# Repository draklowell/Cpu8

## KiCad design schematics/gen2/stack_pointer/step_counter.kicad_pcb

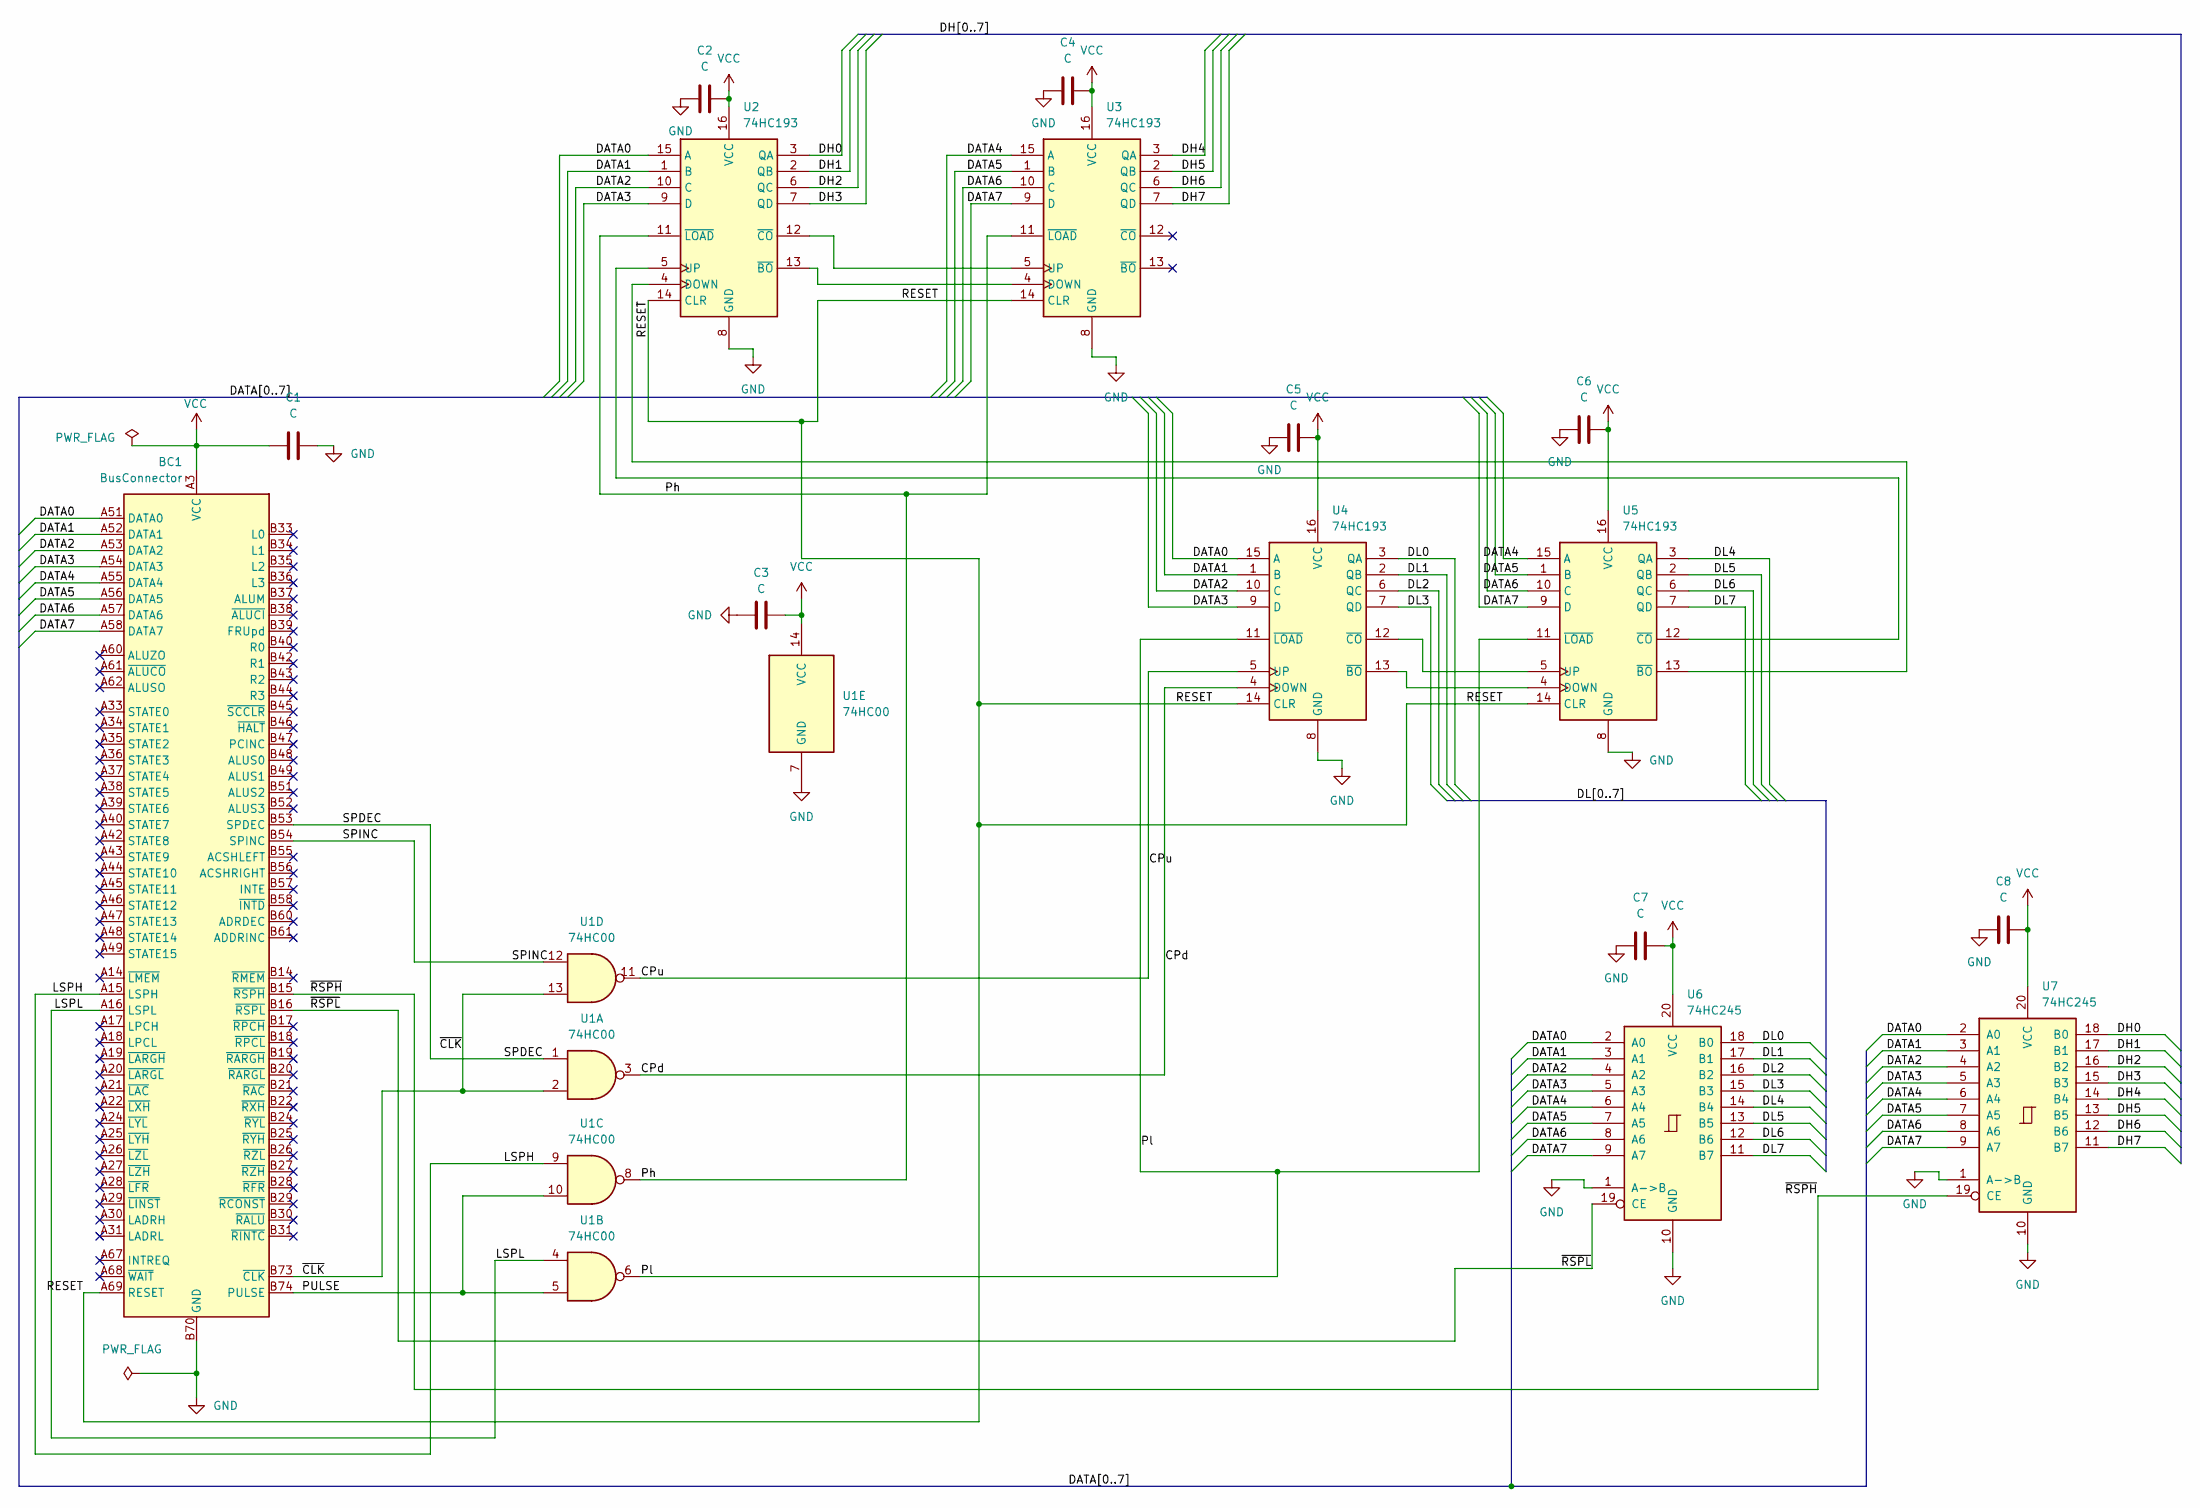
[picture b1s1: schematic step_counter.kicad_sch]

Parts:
BC1: BusConnector; BUS_PCIexpress_x16
C1: C; C_Radial_D6.3mm_H5.0mm_P2.50mm
C2, C3, C4, C5, C6, C7, C8: C; C_Disc_D3.0mm_W1.6mm_P2.50mm
U1: 74HC00; DIP-14_W7.62mm_Socket_LongPads
U2, U3, U4, U5: 74HC193; DIP-16_W7.62mm_Socket_LongPads
U6, U7: 74HC245; DIP-20_W7.62mm_Socket_LongPads

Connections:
/CPd: U1.3, U4.4 (DOWN)
/CPu: U1.11, U4.5 (UP)
/DATA0: BC1.A51 (DATA0), U2.15 (A), U4.15 (A), U6.2 (A0), U7.2 (A0)
/DATA1: BC1.A52 (DATA1), U2.1 (B), U4.1 (B), U6.3 (A1), U7.3 (A1)
/DATA2: BC1.A53 (DATA2), U2.10 (C), U4.10 (C), U6.4 (A2), U7.4 (A2)
/DATA3: BC1.A54 (DATA3), U2.9 (D), U4.9 (D), U6.5 (A3), U7.5 (A3)
/DATA4: BC1.A55 (DATA4), U3.15 (A), U5.15 (A), U6.6 (A4), U7.6 (A4)
/DATA5: BC1.A56 (DATA5), U3.1 (B), U5.1 (B), U6.7 (A5), U7.7 (A5)
/DATA6: BC1.A57 (DATA6), U3.10 (C), U5.10 (C), U6.8 (A6), U7.8 (A6)
/DATA7: BC1.A58 (DATA7), U3.9 (D), U5.9 (D), U6.9 (A7), U7.9 (A7)
/DH0: U2.3 (QA), U7.18 (B0)
/DH1: U2.2 (QB), U7.17 (B1)
/DH2: U2.6 (QC), U7.16 (B2)
/DH3: U2.7 (QD), U7.15 (B3)
/DH4: U3.3 (QA), U7.14 (B4)
/DH5: U3.2 (QB), U7.13 (B5)
/DH6: U3.6 (QC), U7.12 (B6)
/DH7: U3.7 (QD), U7.11 (B7)
/DL0: U4.3 (QA), U6.18 (B0)
/DL1: U4.2 (QB), U6.17 (B1)
/DL2: U4.6 (QC), U6.16 (B2)
/DL3: U4.7 (QD), U6.15 (B3)
/DL4: U5.3 (QA), U6.14 (B4)
/DL5: U5.2 (QB), U6.13 (B5)
/DL6: U5.6 (QC), U6.12 (B6)
/DL7: U5.7 (QD), U6.11 (B7)
/LSPH: BC1.A15 (LSPH), U1.9
/LSPL: BC1.A16 (LSPL), U1.4
/PULSE: BC1.B74 (PULSE), U1.5, U1.10
/Ph: U1.8, U2.11 (~LOAD), U3.11 (~LOAD)
/Pl: U1.6, U4.11 (~LOAD), U5.11 (~LOAD)
/RESET: BC1.A69 (RESET), U2.14 (CLR), U3.14 (CLR), U4.14 (CLR), U5.14 (CLR)
/SPDEC: BC1.B53 (SPDEC), U1.1
/SPINC: BC1.B54 (SPINC), U1.12
/~CLK: BC1.B73 (~CLK), U1.2, U1.13
/~RSPH: BC1.B15 (~RSPH), U7.19 (CE)
/~RSPL: BC1.B16 (~RSPL), U6.19 (CE)
GND: BC1.A12 (GND), BC1.A13 (GND), BC1.A23 (GND), BC1.A32 (GND), BC1.A41 (GND), BC1.A50 (GND), BC1.A59 (GND), BC1.A63 (GND), BC1.A64 (GND), BC1.A65 (GND), BC1.A66 (GND), BC1.A70 (GND), BC1.A71 (GND), BC1.A72 (GND), BC1.A73 (GND), BC1.A74 (GND), BC1.A75 (GND), BC1.A76 (GND), BC1.B12 (GND), BC1.B13 (GND), BC1.B23 (GND), BC1.B32 (GND), BC1.B41 (GND), BC1.B50 (GND), BC1.B59 (GND), BC1.B62 (GND), BC1.B63 (GND), BC1.B64 (GND), BC1.B65 (GND), BC1.B66 (GND), BC1.B67 (GND), BC1.B68 (GND), BC1.B69 (GND), BC1.B70 (GND), BC1.B71 (GND), BC1.B72 (GND), BC1.B75 (GND), BC1.B76 (GND), C1.2, C2.1, C3.1, C4.1, C5.1, C6.1, C7.2, C8.2, U1.7 (GND), U2.8 (GND), U3.8 (GND), U4.8 (GND), U5.8 (GND), U6.1 (A->B), U6.10 (GND), U7.1 (A->B), U7.10 (GND)
unnamed: U2.4 (DOWN), U5.13 (~BO)
unnamed: U2.5 (UP), U5.12 (~CO)
unnamed: U2.13 (~BO), U3.4 (DOWN)
unnamed: U2.12 (~CO), U3.5 (UP)
unnamed: U4.13 (~BO), U5.4 (DOWN)
unnamed: U4.12 (~CO), U5.5 (UP)
VCC: BC1.A1 (VCC), BC1.A2 (VCC), BC1.A3 (VCC), BC1.A4 (VCC), BC1.A5 (VCC), BC1.B1 (VCC), BC1.B2 (VCC), BC1.B3 (VCC), BC1.B4 (VCC), BC1.B5 (VCC), C1.1, C2.2, C3.2, C4.2, C5.2, C6.2, C7.1, C8.1, U1.14 (VCC), U2.16 (VCC), U3.16 (VCC), U4.16 (VCC), U5.16 (VCC), U6.20 (VCC), U7.20 (VCC)

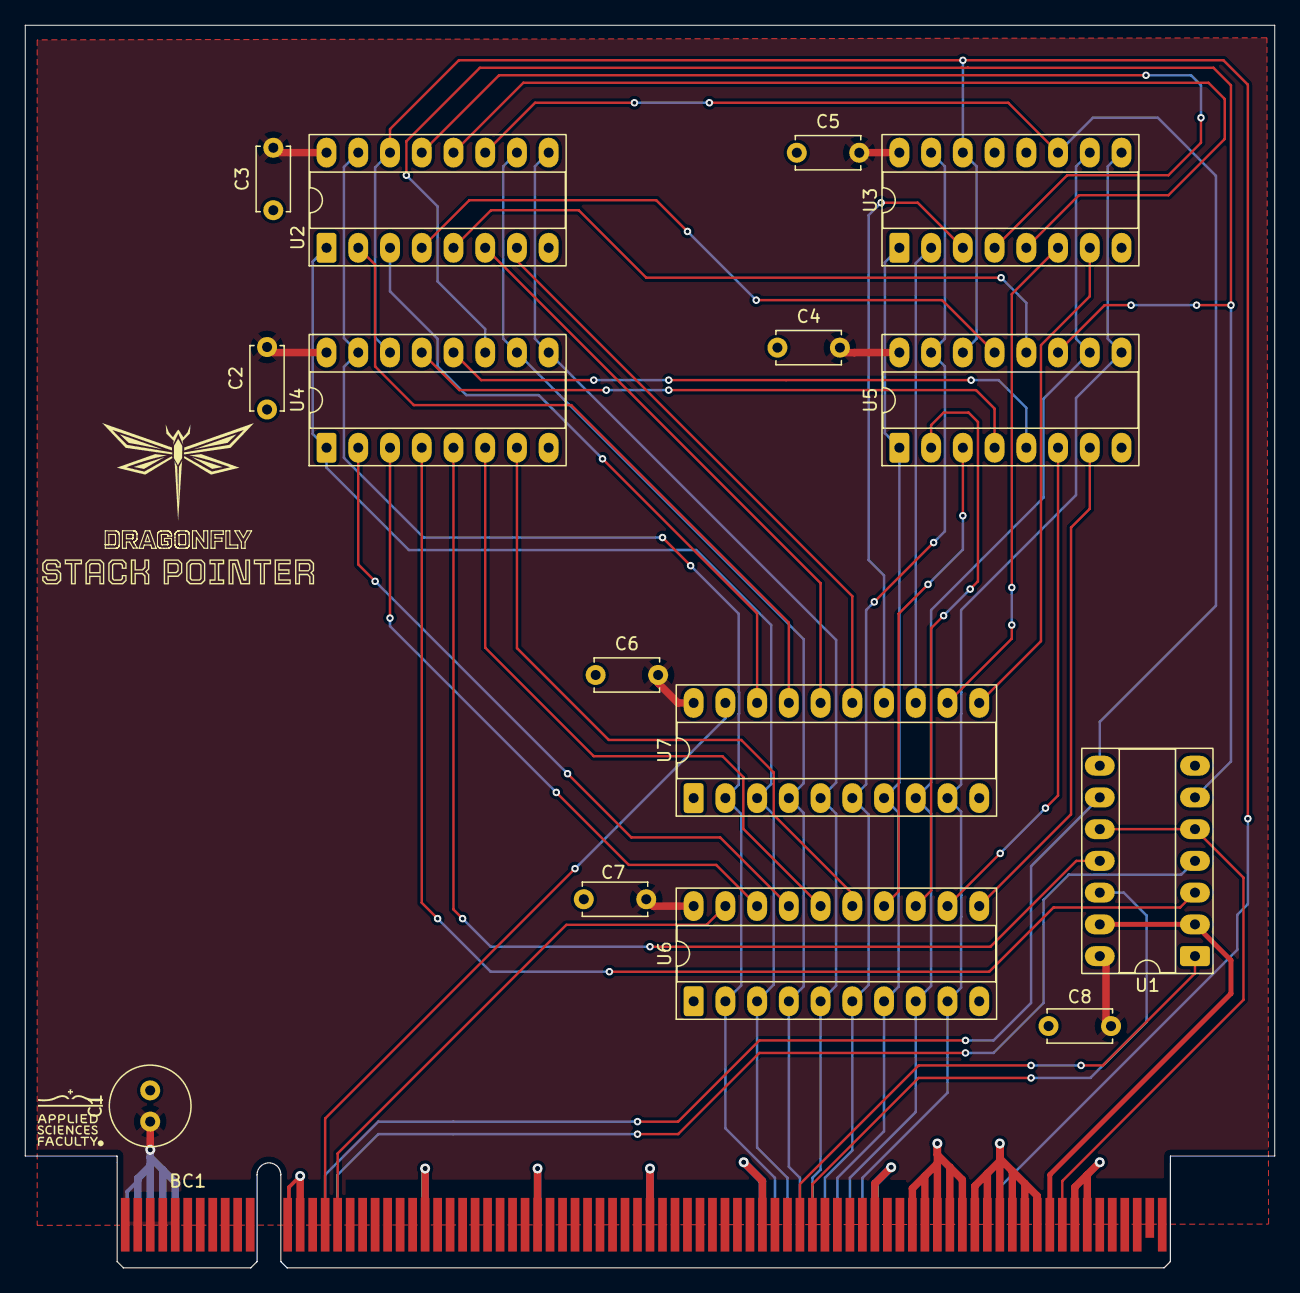
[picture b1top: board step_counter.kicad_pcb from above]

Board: 2 copper layers, 100.0 x 99.4 mm, 17 parts (0 on the bottom side), 45 nets.

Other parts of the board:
kibuzzard-6911C575: G***; kibuzzard-6911C575

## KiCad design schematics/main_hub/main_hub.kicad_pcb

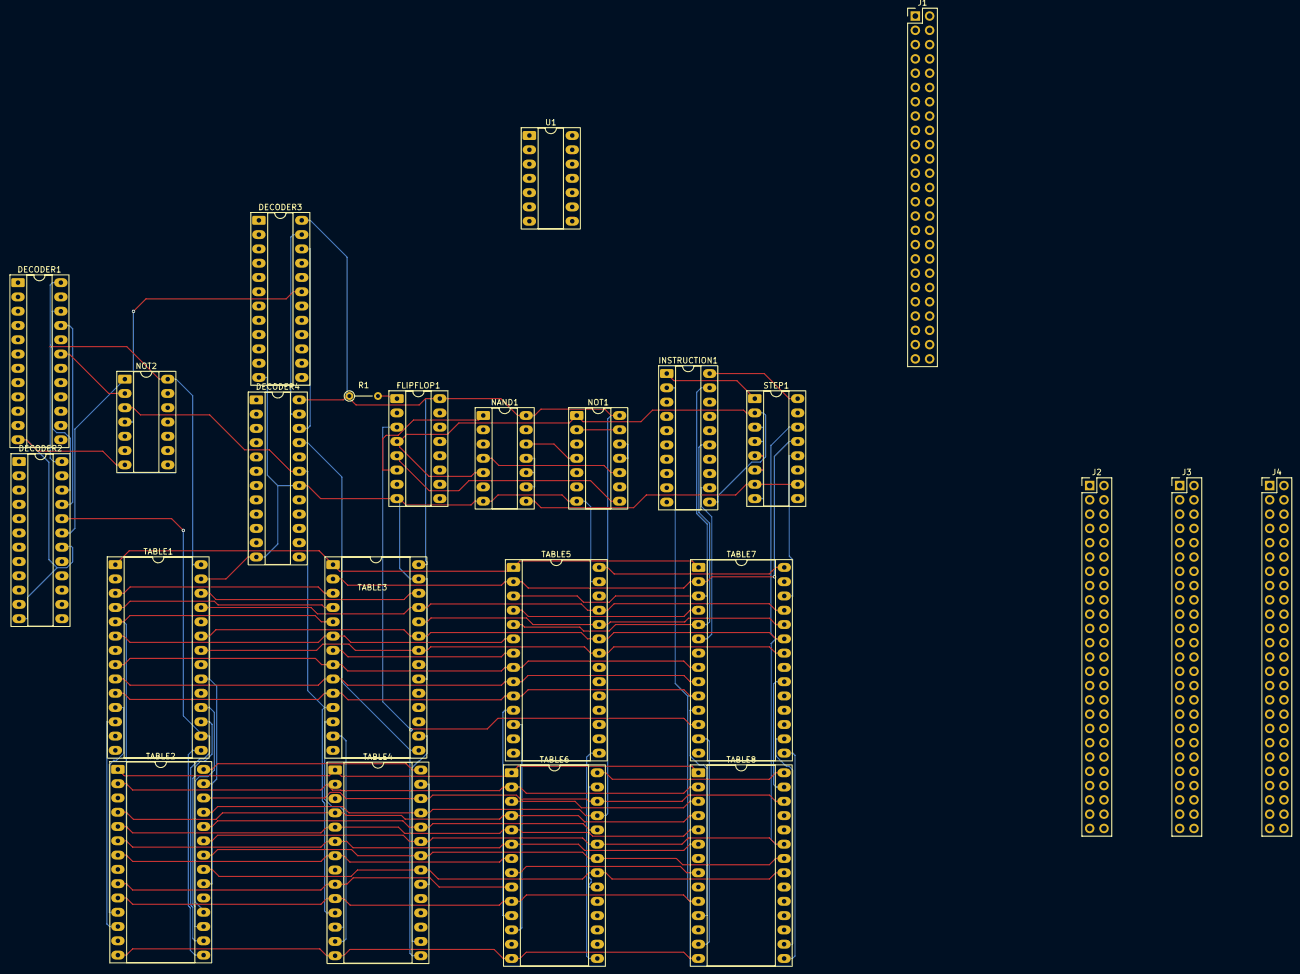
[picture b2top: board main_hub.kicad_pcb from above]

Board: 2 copper layers, 24 parts (0 on the bottom side), 90 nets.

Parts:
DECODER1, DECODER2, DECODER3, DECODER4: 74LS154; DIP-24_W7.62mm_Socket_LongPads
FLIPFLOP1: 74LS109; DIP-16_W7.62mm_Socket_LongPads
INSTRUCTION1: 74LS273; DIP-20_W7.62mm_Socket_LongPads
J1, J2, J3, J4: Conn_02x25_Counter_Clockwise; PinHeader_2x25_P2.54mm_Vertical
NAND1: 74LS00; DIP-14_W7.62mm_Socket_LongPads
NOT1, NOT2: 74LS04; DIP-14_W7.62mm_Socket_LongPads
R1: 5kOhm; R_Axial_DIN0204_L3.6mm_D1.6mm_P5.08mm_Vertical
STEP1: 74LS161; DIP-16_W7.62mm_Socket_LongPads
TABLE1, TABLE2, TABLE3, TABLE4, TABLE5, TABLE6, TABLE7, TABLE8: 28C256; DIP-28_W15.24mm_Socket_LongPads
U1: 74LS02; DIP-14_W7.62mm_Socket_LongPads

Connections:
/ALUM: J1.31, TABLE1.17 (D5), TABLE2.17 (D5)
/ALUS0: J1.35, TABLE5.11 (D0), TABLE6.11 (D0)
/ALUS1: J1.34, TABLE5.12 (D1), TABLE6.12 (D1)
/ALUS2: J1.33, TABLE5.13 (D2), TABLE6.13 (D2)
/ALUS3: J1.32, TABLE5.15 (D3), TABLE6.15 (D3)
/ALUSignOut: J1.38, J2.23
/ALUZeroOut: J1.36, J2.21
/AccumShiftLeft: J1.29, TABLE5.18 (D6), TABLE6.18 (D6)
/AccumShiftRight: J1.28, TABLE5.19 (D7), TABLE6.19 (D7)
/AddrDecrement: TABLE7.13 (D2), TABLE8.13 (D2)
/AddrIncrement: TABLE7.15 (D3), TABLE8.15 (D3)
/BUS0: INSTRUCTION1.3 (D0), J1.11, J2.11, J3.11, J4.11
/BUS1: INSTRUCTION1.4 (D1), J1.12, J2.12, J3.12, J4.12
/BUS2: INSTRUCTION1.7 (D2), J1.13, J2.13, J3.13, J4.13
/BUS3: INSTRUCTION1.8 (D3), J1.14, J2.14, J3.14, J4.14
/BUS4: INSTRUCTION1.13 (D4), J1.15, J2.15, J3.15, J4.15
/BUS5: INSTRUCTION1.14 (D5), J1.16, J2.16, J3.16, J4.16
/BUS6: INSTRUCTION1.17 (D6), J1.17, J2.17, J3.17, J4.17
/BUS7: INSTRUCTION1.18 (D7), J1.18, J2.18, J3.18, J4.18
/Clk: FLIPFLOP1.4 (C), J1.4, J2.4, J3.4, J4.4, NAND1.5, NOT1.1, STEP1.2 (CP)
/IntEnable: FLIPFLOP1.2 (J), TABLE7.11 (D0), TABLE8.11 (D0)
/PCIncrement: TABLE3.19 (D7), TABLE4.19 (D7)
/Pulse: J1.48, J2.48, J3.48, J4.48, NAND1.6
/SPDecrement: TABLE5.16 (D4), TABLE6.16 (D4)
/SPIncrement: TABLE5.17 (D5), TABLE6.17 (D5)
/STATE0: INSTRUCTION1.2 (Q0), TABLE1.10 (A0), TABLE2.10 (A0), TABLE3.10 (A0), TABLE4.10 (A0), TABLE5.10 (A0), TABLE6.10 (A0), TABLE7.10 (A0), TABLE8.10 (A0)
/STATE1: INSTRUCTION1.5 (Q1), TABLE1.9 (A1), TABLE2.9 (A1), TABLE3.9 (A1), TABLE4.9 (A1), TABLE5.9 (A1), TABLE6.9 (A1), TABLE7.9 (A1), TABLE8.9 (A1)
/STATE2: INSTRUCTION1.6 (Q2), TABLE1.8 (A2), TABLE2.8 (A2), TABLE3.8 (A2), TABLE4.8 (A2), TABLE5.8 (A2), TABLE6.8 (A2), TABLE7.8 (A2), TABLE8.8 (A2)
/STATE3: INSTRUCTION1.9 (Q3), TABLE1.7 (A3), TABLE2.7 (A3), TABLE3.7 (A3), TABLE4.7 (A3), TABLE5.7 (A3), TABLE6.7 (A3), TABLE7.7 (A3), TABLE8.7 (A3)
/STATE4: INSTRUCTION1.12 (Q4), TABLE1.6 (A4), TABLE2.6 (A4), TABLE3.6 (A4), TABLE4.6 (A4), TABLE5.6 (A4), TABLE6.6 (A4), TABLE7.6 (A4), TABLE8.6 (A4)
/STATE5: INSTRUCTION1.15 (Q5), TABLE1.5 (A5), TABLE2.5 (A5), TABLE3.5 (A5), TABLE4.5 (A5), TABLE5.5 (A5), TABLE6.5 (A5), TABLE7.5 (A5), TABLE8.5 (A5)
/STATE6: INSTRUCTION1.16 (Q6), TABLE1.4 (A6), TABLE2.4 (A6), TABLE3.4 (A6), TABLE4.4 (A6), TABLE5.4 (A6), TABLE6.4 (A6), TABLE7.4 (A6), TABLE8.4 (A6)
/STATE7: INSTRUCTION1.19 (Q7), TABLE1.3 (A7), TABLE2.3 (A7), TABLE3.3 (A7), TABLE4.3 (A7), TABLE5.3 (A7), TABLE6.3 (A7), TABLE7.3 (A7), TABLE8.3 (A7)
/STATE8: J2.44, TABLE1.25 (A8), TABLE2.25 (A8), TABLE3.25 (A8), TABLE4.25 (A8), TABLE5.25 (A8), TABLE6.25 (A8), TABLE7.25 (A8), TABLE8.25 (A8)
/STATE9: J2.45, TABLE1.24 (A9), TABLE2.24 (A9), TABLE3.24 (A9), TABLE4.24 (A9), TABLE5.24 (A9), TABLE6.24 (A9), TABLE7.24 (A9), TABLE8.24 (A9)
/STATE10: J2.46, TABLE1.21 (A10), TABLE2.21 (A10), TABLE3.21 (A10), TABLE4.21 (A10), TABLE5.21 (A10), TABLE6.21 (A10), TABLE7.21 (A10), TABLE8.21 (A10)
/STATE11: STEP1.14 (Q0), TABLE1.23 (A11), TABLE2.23 (A11), TABLE3.23 (A11), TABLE4.23 (A11), TABLE5.23 (A11), TABLE6.23 (A11), TABLE7.23 (A11), TABLE8.23 (A11)
/STATE12: STEP1.13 (Q1), TABLE1.2 (A12), TABLE2.2 (A12), TABLE3.2 (A12), TABLE4.2 (A12), TABLE5.2 (A12), TABLE6.2 (A12), TABLE7.2 (A12), TABLE8.2 (A12)
/STATE13: STEP1.12 (Q2), TABLE1.26 (A13), TABLE2.26 (A13), TABLE3.26 (A13), TABLE4.26 (A13), TABLE5.26 (A13), TABLE6.26 (A13), TABLE7.26 (A13), TABLE8.26 (A13)
/STATE14: STEP1.11 (Q3), TABLE1.1 (A14), TABLE2.1 (A14), TABLE3.1 (A14), TABLE4.1 (A14), TABLE5.1 (A14), TABLE6.1 (A14), TABLE7.1 (A14), TABLE8.1 (A14)
/STATE15: NOT1.6, TABLE1.22 (~OE), TABLE3.22 (~OE), TABLE5.22 (~OE), TABLE7.22 (~OE)
/STATE16: NAND1.3, NOT1.5, TABLE2.22 (~OE), TABLE4.22 (~OE), TABLE6.22 (~OE), TABLE8.22 (~OE)
/~ALUCarryIn: J1.30, TABLE1.18 (D6), TABLE2.18 (D6)
/~ALUCarryOut: J1.37, J2.22
/~ALUWriter: DECODER4.1 (S0), J1.39
/~AccumReader: DECODER1.9 (S8), J1.46, NOT2.11
/~AccumWriter: DECODER3.9 (S8), J1.27, NOT2.9
/~Clk: J1.3, J2.3, J3.3, J4.3, NOT1.2, NOT1.13, U1.2
/~FlagsReader: DECODER1.16 (S14), J2.34
/~FlagsUpdate: J2.28, TABLE1.19 (D7), TABLE2.19 (D7)
/~FlagsWriter: DECODER3.16 (S14), J2.40
/~Halt: NAND1.13, TABLE3.18 (D6), TABLE4.18 (D6)
/~InstructionReader: DECODER1.17 (S15), U1.3
/~IntDisable: FLIPFLOP1.3 (~K), TABLE7.12 (D1), TABLE8.12 (D1)
/~Reset: FLIPFLOP1.5 (~S), INSTRUCTION1.1 (~Mr), NOT1.8, STEP1.1 (~MR)
/~SCClear: STEP1.9 (~PE), TABLE3.17 (D5), TABLE4.17 (D5)
/~TemporaryHighReader: DECODER1.7 (S6), J1.40, NOT2.13
/~TemporaryHighWriter: DECODER3.7 (S6), J1.41
/~XHReader: DECODER1.10 (S9), J2.33
/~XHWriter: DECODER3.10 (S9), J2.39
/~YHReader: DECODER1.13 (S11), J2.31
/~YHWriter: DECODER3.13 (S11), J2.37
/~YLReader: DECODER1.11 (S10), J2.32
/~YLWriter: DECODER3.11 (S10), J2.38
/~ZHReader: DECODER1.15 (S13), J2.29
/~ZHWriter: DECODER3.15 (S13), J2.35
/~ZLReader: DECODER1.14 (S12), J2.30
/~ZLWriter: DECODER3.14 (S12), J2.36
GND: DECODER1.12 (GND), DECODER1.18 (E0), DECODER2.12 (GND), DECODER2.18 (E0), DECODER3.12 (GND), DECODER3.18 (E0), DECODER4.12 (GND), DECODER4.18 (E0), FLIPFLOP1.8 (GND), INSTRUCTION1.10 (GND), J1.2, J1.10, J1.19, J1.49, J2.2, J2.10, J2.19, J2.49, J3.2, J3.10, J3.19, J3.49, J4.2, J4.10, J4.19, J4.49, NAND1.7 (GND), NOT1.7 (GND), NOT2.7 (GND), STEP1.3 (D0), STEP1.4 (D1), STEP1.5 (D2), STEP1.6 (D3), STEP1.8 (GND), TABLE1.14 (GND), TABLE1.20 (~CS), TABLE1.27 (~WE), TABLE2.14 (GND), TABLE2.20 (~CS), TABLE2.27 (~WE), TABLE3.14 (GND), TABLE3.20 (~CS), TABLE3.27 (~WE), TABLE4.14 (GND), TABLE4.20 (~CS), TABLE4.27 (~WE), TABLE5.14 (GND), TABLE5.20 (~CS), TABLE5.27 (~WE), TABLE6.14 (GND), TABLE6.20 (~CS), TABLE6.27 (~WE), TABLE7.14 (GND), TABLE7.20 (~CS), TABLE7.27 (~WE), TABLE8.14 (GND), TABLE8.20 (~CS), TABLE8.27 (~WE), U1.7 (GND)
unnamed: DECODER1.23 (A0), DECODER2.23 (A0), TABLE1.12 (D1), TABLE2.12 (D1)
unnamed: DECODER1.22 (A1), DECODER2.22 (A1), TABLE1.13 (D2), TABLE2.13 (D2)
unnamed: DECODER1.21 (A2), DECODER2.21 (A2), TABLE1.15 (D3), TABLE2.15 (D3)
unnamed: DECODER1.20 (A3), DECODER2.20 (A3), TABLE1.16 (D4), TABLE2.16 (D4)
unnamed: DECODER1.19 (E1), NOT2.2, U1.10
unnamed: DECODER2.19 (E1), NOT2.1, TABLE1.11 (D0), TABLE2.11 (D0), U1.8, U1.9
unnamed: DECODER3.23 (A0), DECODER4.23 (A0), TABLE3.12 (D1), TABLE4.12 (D1)
unnamed: DECODER3.22 (A1), DECODER4.22 (A1), TABLE3.13 (D2), TABLE4.13 (D2)
unnamed: DECODER3.21 (A2), DECODER4.21 (A2), TABLE3.15 (D3), TABLE4.15 (D3)
unnamed: DECODER3.20 (A3), DECODER4.20 (A3), TABLE3.16 (D4), TABLE4.16 (D4)
unnamed: DECODER3.19 (E1), NOT2.4, U1.4
unnamed: DECODER4.19 (E1), NOT2.3, TABLE3.11 (D0), TABLE4.11 (D0), U1.5, U1.6
unnamed: FLIPFLOP1.6 (Q), NAND1.1
unnamed: FLIPFLOP1.1 (~R), R1.2
unnamed: INSTRUCTION1.11 (Cp), U1.1
unnamed: NAND1.4, NOT1.10
unnamed: NAND1.9, NAND1.10, NAND1.11
unnamed: NAND1.12, NOT1.4
unnamed: NOT1.11, NOT1.12
unnamed: NAND1.8, STEP1.7 (CEP), STEP1.10 (CET)
VCC: DECODER1.24 (VCC), DECODER2.24 (VCC), DECODER3.24 (VCC), DECODER4.24 (VCC), FLIPFLOP1.16 (VCC), INSTRUCTION1.20 (VCC), J1.1, J1.25, J1.26, J1.50, J2.1, J2.25, J2.26, J2.50, J3.1, J3.25, J3.26, J3.50, J4.1, J4.25, J4.26, J4.50, NAND1.14 (VCC), NOT1.14 (VCC), NOT2.14 (VCC), R1.1, STEP1.16 (VCC), TABLE1.28 (VCC), TABLE2.28 (VCC), TABLE3.28 (VCC), TABLE4.28 (VCC), TABLE5.28 (VCC), TABLE6.28 (VCC), TABLE7.28 (VCC), TABLE8.28 (VCC), U1.14 (VCC)
